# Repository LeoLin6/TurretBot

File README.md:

# TurretBot for automated acoustic experiments. 

Already have the hardware setup? Jump to the [Software section](#Software).

## Sourcing the parts

#### 🧾 Fabrication Files

All files required for manufacturing the PCB can be found here:  
👉 [PCB Manufacturing Files](./tmc%20pcb%20manufacturing%20files/feb2025_fab)

#### 🔩 Component List

| Part Name                                                | Quantity | Designation on Schematic         | Link                                                                 |
|----------------------------------------------------------|----------|----------------------------------|----------------------------------------------------------------------|
| Barrel Jack for power                                    | 1        | J1 (Barrel_Jack)                 | [digikey](https://www.digikey.com/en/products/detail/same-sky-formerly-cui-devices/PJ-002A/96962)           |
| PinSocket headers for Arduino Nano                       | 2        | J3, J5                            | [digikey](https://www.digikey.com/en/products/detail/sullins-connector-solutions/PPTC151LFBN-RC/810153)     |
| PinSocket headers for TMC 2208 driver chip               | 2        | J4, J6                            | [digikey](https://www.digikey.com/en/products/detail/w%C3%BCrth-elektronik/61300811821/17737805)            |
| Induction sensor terminal block                          | 1        | J7                                | [digikey](https://www.digikey.com/en/products/detail/phoenix-contact/1715734/260632)                        |
| Terminal Block for stepper motor                         | 1        | J2 (Screw_Terminal for motor)     | [digikey](https://www.digikey.com/en/products/detail/phoenix-contact/1715747/260633)                        |
|TMC 2208 motor driver chip                                 | 1        |  None                            | [digikey](https://www.digikey.com/short/j84mhvfm)|
| Adafruit adjustable power supply  (Run it at 18 Volts)            | 1         | None                                | [digikey](https://www.digikey.com/short/31r0mw15)  |
| Induction sensor                                      | 1         | None                                  | [amazon](https://www.amazon.com/Taiss-NO%EF%BC%88Normally-LJ12A3-4-Z-inductive-Proximity/dp/B073XD44CW) |

## 🔧 Assembly Instructions

Follow the designators on this PCB to solder the parts above: ([also have schematic for reference](./images/pcb_v2_schematic.png))

Final assembled PCB:

For motor connector reference (What's color code M1B, M1A etc)

Follow this github tutorial to Solder UART bridge on tmc 2208 chip:
https://github.com/teemuatlut/TMC2208Stepper?tab=readme-ov-file

## Software

### 1. Clone the Repository
```bash
git clone https://github.com/LeoLin6/TurretBot.git
cd TurretBot
```

### 2. Install Arduino IDE

If you don't already have the Arduino IDE installed, download and install it from the official website:  
🔗 [https://www.arduino.cc/en/software](https://www.arduino.cc/en/software)

### 3. Flash the Arduino

1. **Open Arduino IDE**  
2. **Go to:**  
   `File` → `Open` → Navigate to `TurretBot/main/src/experiment_arduino/experiment_arduino.ino`
3. **Connect your Arduino** via USB to your PC.
4. **Select the correct board and port**:  
   - `Tools` → `Board` → Select the correct Arduino board (e.g., Arduino Uno)  
   - `Tools` → `Port` → Select the appropriate COM port (note it down, you'll need it for the next step)  
5. **Click Upload** (the right-arrow icon) to flash the firmware to the Arduino.

### 4. Run the Python Script for Calibration

1. Make sure you have Python installed (preferably Python 3.x).  
2. Navigate to the script directory:
```bash
cd main/src
```
3. Run the script:
```bash
python experiment.py
```
4. Follow the terminal prompts for calibration and testing positional movement.

> 💡 Make sure the COM port in the script matches the one your Arduino is using.

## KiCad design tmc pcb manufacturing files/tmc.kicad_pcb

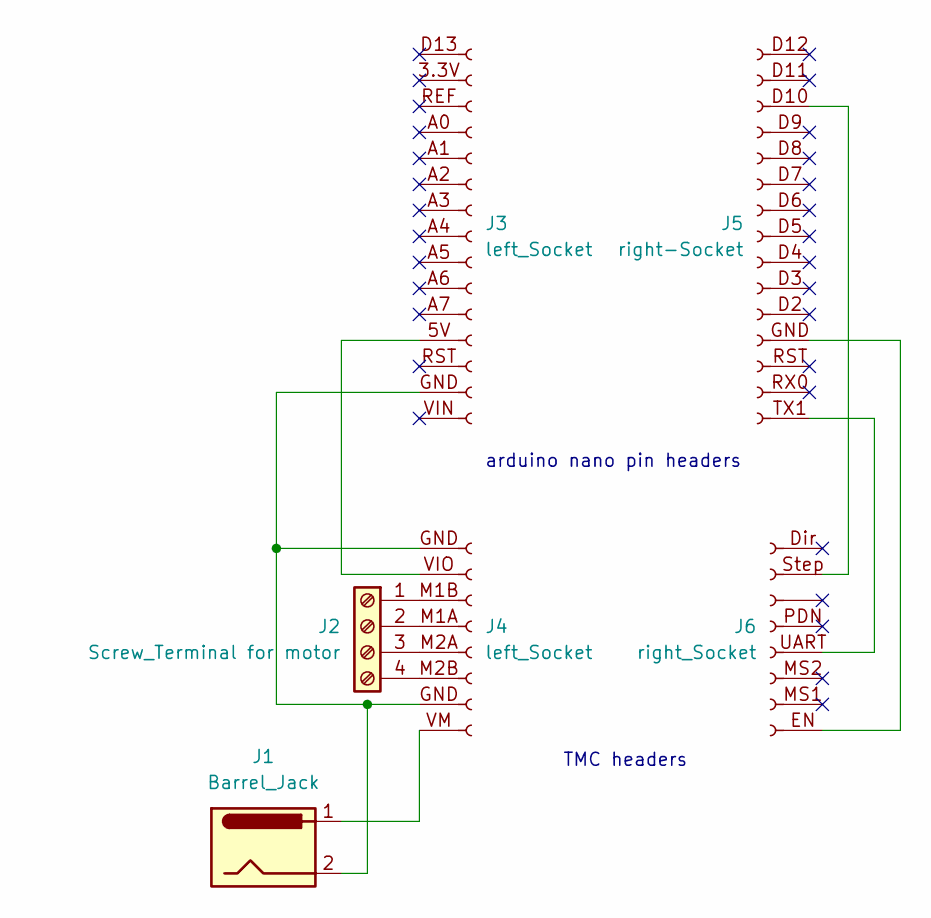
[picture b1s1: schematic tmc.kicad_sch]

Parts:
J1: Barrel_Jack; BarrelJack_Horizontal
J2: Screw_Terminal for motor; TerminalBlock_Phoenix_MKDS-1,5-4_1x04_P5.00mm_Horizontal
J3: left_Socket; PinSocket_1x15_P2.54mm_Vertical
J4: left_Socket; PinSocket_1x08_P2.54mm_Vertical
J5: right-Socket; PinSocket_1x15_P2.54mm_Vertical
J6: right_Socket; PinSocket_1x08_P2.54mm_Vertical

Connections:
unnamed: J2.1, J4.M1B (Pin_3)
unnamed: J2.2, J4.M1A (Pin_4)
unnamed: J2.3, J4.M2A (Pin_5)
unnamed: J2.4, J4.M2B (Pin_6)
unnamed: J3.5V (Pin_12), J4.VIO (Pin_2)
unnamed: J1.2, J3.GND (Pin_14), J4.GND (Pin_1)
unnamed: J1.1, J4.VM (Pin_8)
unnamed: J5.D10 (Pin_3), J6.Step (Pin_2)
unnamed: J5.GND (Pin_12), J6.EN (Pin_8)
unnamed: J5.TX1 (Pin_15), J6.UART (Pin_5)

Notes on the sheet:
TMC headers
arduino nano pin headers

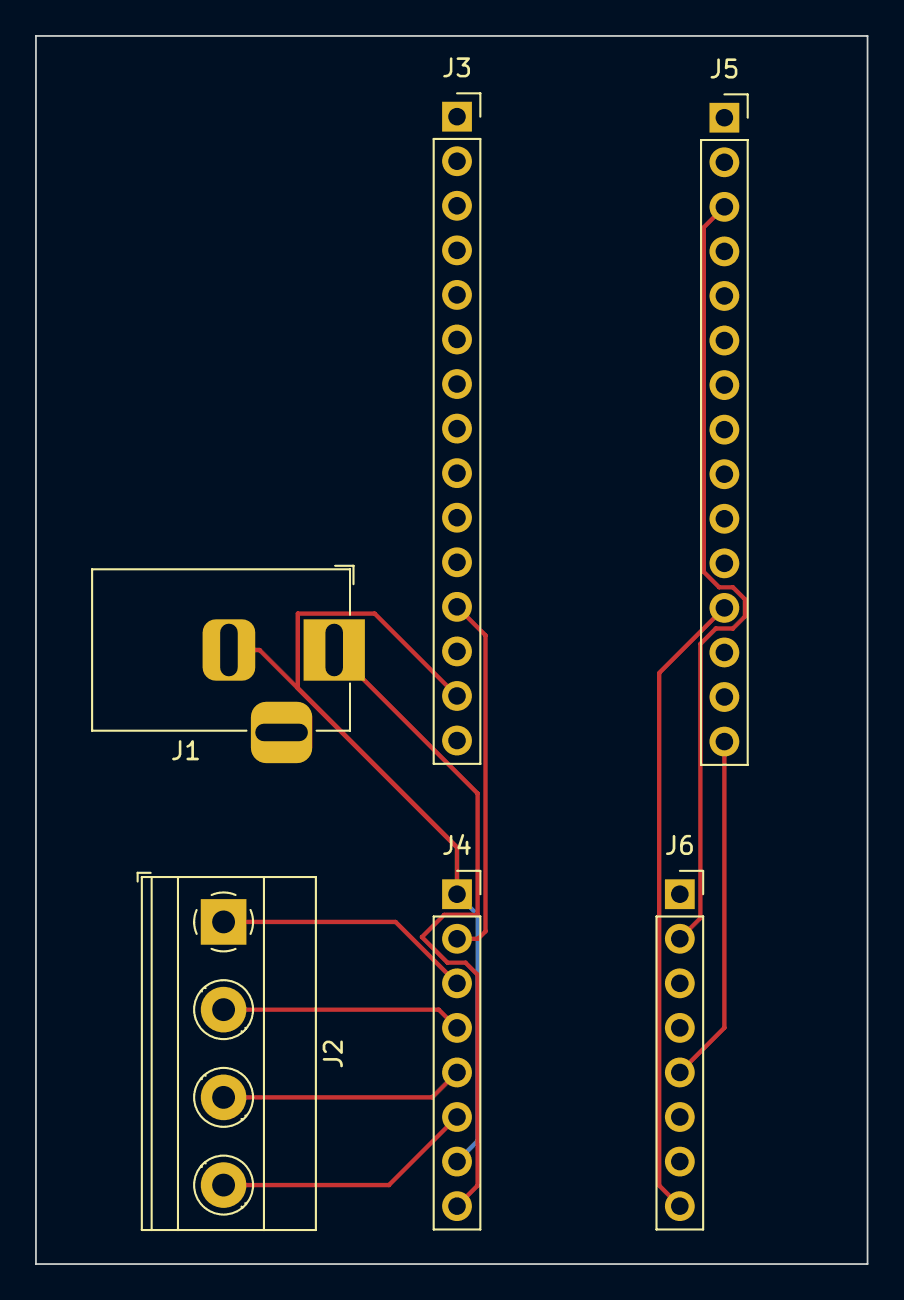
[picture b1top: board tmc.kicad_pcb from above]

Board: 2 copper layers, 47.4 x 70.0 mm, 6 parts (0 on the bottom side), 10 nets.

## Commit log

2024-02-21 Create turret_control_accel.ino
    How to use accel stepper library to control a turret w/ two stepper motors.
2024-09-13 Add files via upload
    Last year's more polished files for the final acoustic tests of turrets in different configurations. Also motor testing with diff drivers
2025-02-03 updated
    yeah
2025-02-07 new project for semester: turntable on pcb
2025-02-21 ver_2_fab_files
    uploaded fabrication files for pcb version 2
2025-02-21 changed BOM
2025-03-28 added schematic file
2025-03-28 Updated schematic with induction sensor wirings
2025-03-28 schematic
2025-03-28 updated color code
2025-04-17 new commit
2025-04-17 not a MAC user
2025-05-06 added turret photo
